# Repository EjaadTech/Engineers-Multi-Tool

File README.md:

# Engineers-Multi-Tool
yet another tool for electronics engineers to use on their workbench - planned to include Voltmeter, Ammeter, Component Tester, Serial Terminal, DAQ functionality, Waveform Generator.

A basic Arduino nano based portable device, having portable power, a basic display and circuitry to measure voltage, current, pulses, test components (Resistors, Capacitors, Transistors and more) and also be able to serve as a Serial Terminal and MORE.

## Planned Features
* Handheld formfactor - credit card/gameboy/mobile phone sized
* Arduino based
* Input Push Buttons - 6 to 10 buttons via 1 single ADC pin
* Nokia Graphics LCD - Mono, Mobile LCD for Display
* Voltage Input - 0 to 50V or possibly, -50 to 50V Voltmeter (2x)
* Current Input - 0 to 500mA or even possibly 1A Ammeter (FUSED)
* Serial Terminal - Show incoming Serial data on screen (adjustable/auto baudrate)
* Sqaure Wave Generator - basic clock generator, upto 1MHz with adjustable Duty Cycle
* Pulse Counter - Basic Pulse stats - Freq, Duty Cycle, etc
* Component Tester - a variant of the SemiConductor Tester
* Battery Powered - Chargeable via USB
* Serial Connection with PC - A basic data acquisition app on PC Side - Windows/Linux

### Suggest any other ideas that could be done..!

## TODO
* Upload Schematic
* Battery Charger integration
* Serial Terminal implementation
* Write more TODO List items...!

## WORK LOG
* Basic Circuit made on a protoboard
* LCD and Buttons Tested
* Simple Voltmeter 0.5 to 50V implemented
* Simple Pulse Generator Implemented with adjustable Freq/Duty
* Simple Menu interface implemented
* Integrate the Voltmeter, Pulse generator and Menu in one code
> DONE before 10th of June 2015

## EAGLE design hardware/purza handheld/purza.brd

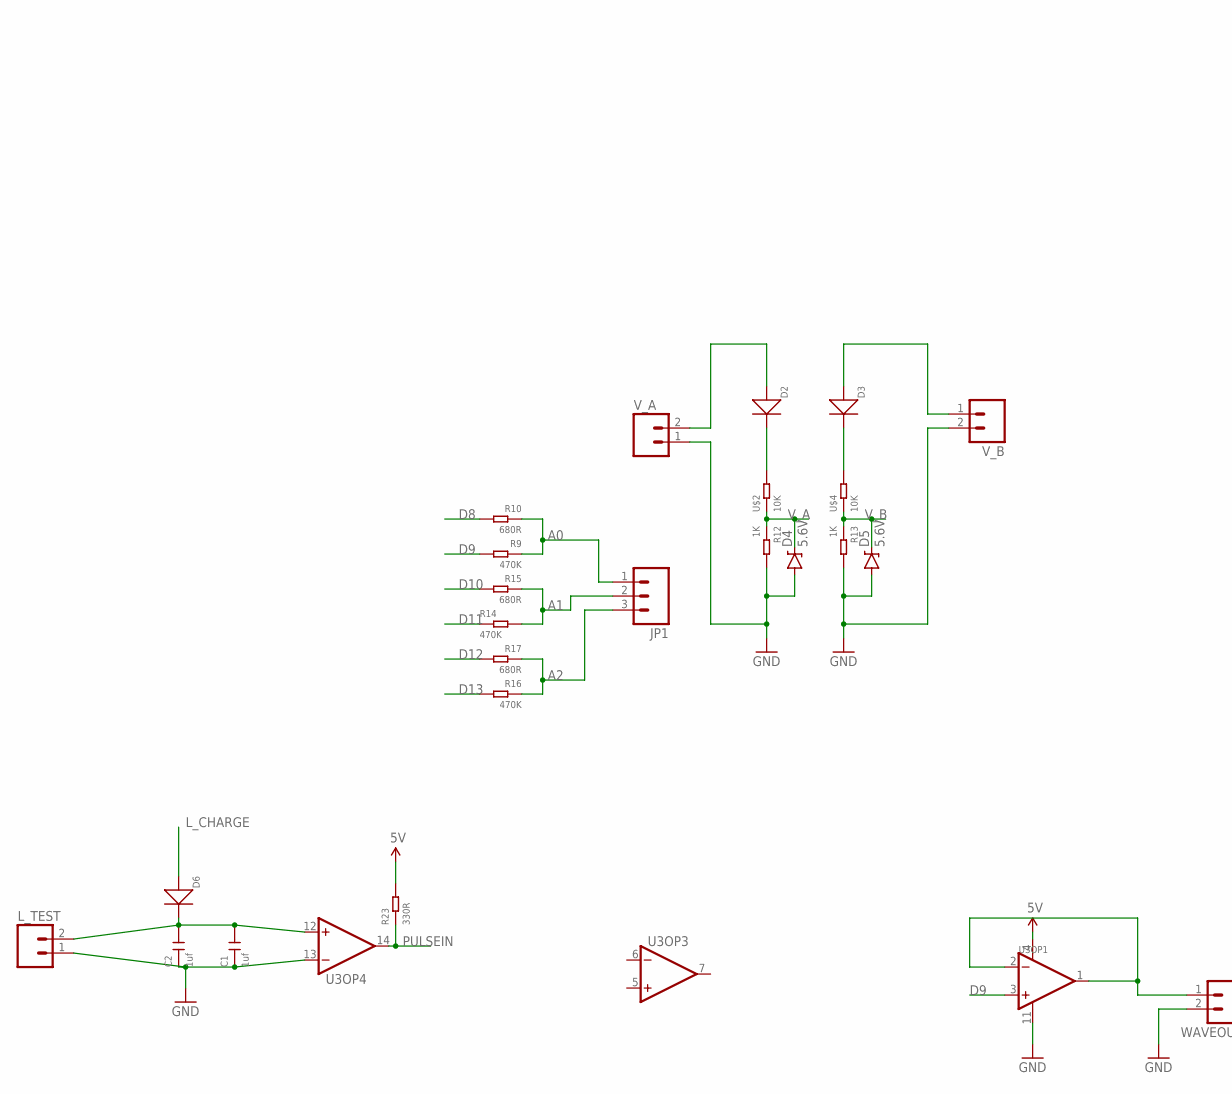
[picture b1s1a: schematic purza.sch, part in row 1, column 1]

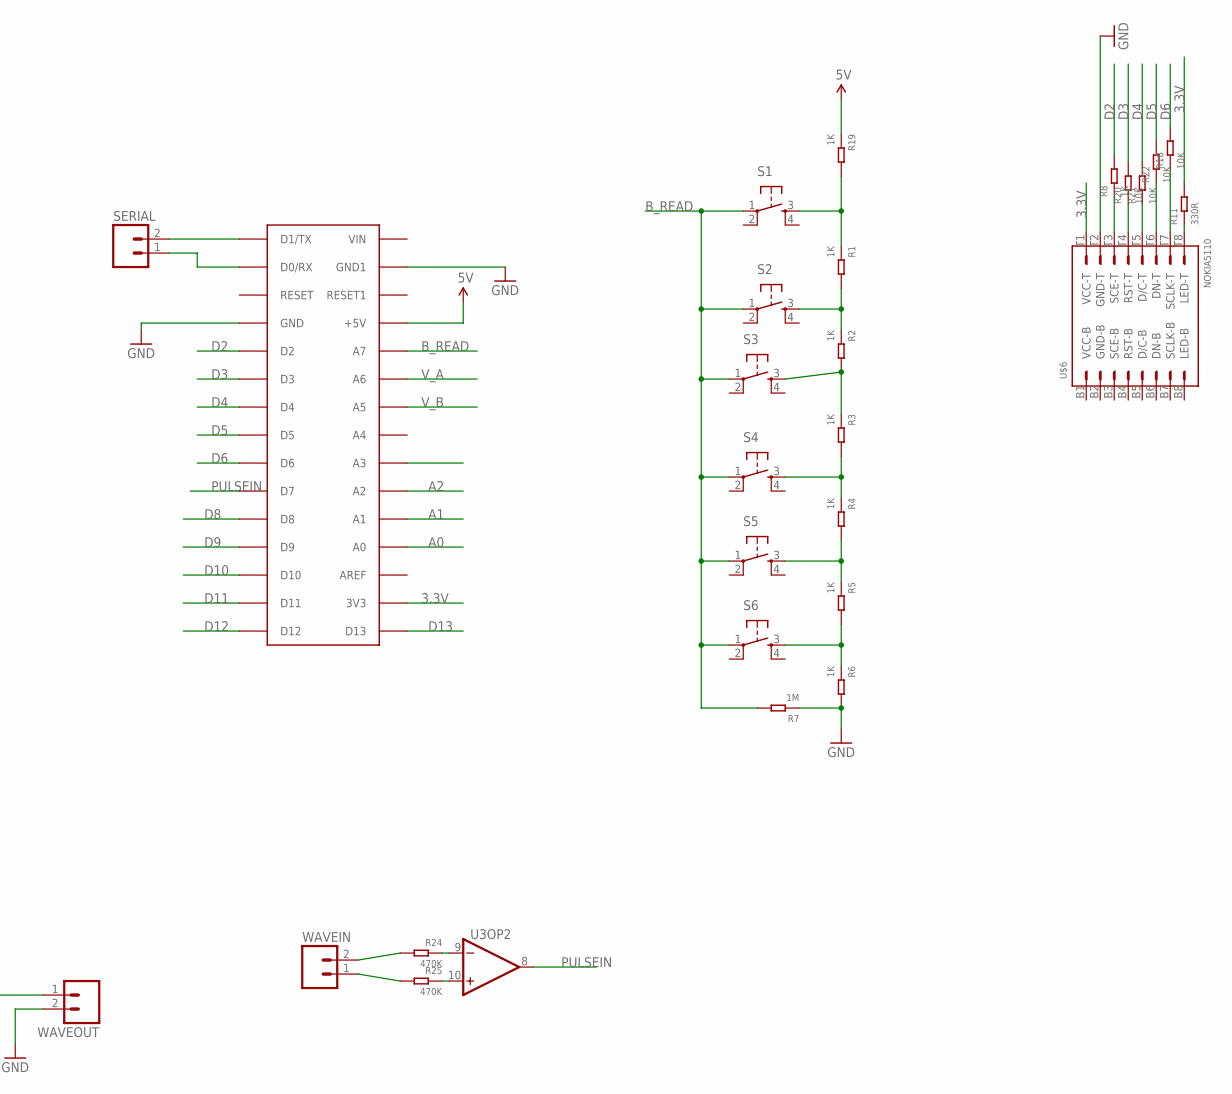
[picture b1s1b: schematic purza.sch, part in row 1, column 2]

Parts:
C1, C2: 1uf; C0805
D2, D3, D6: DIODE'1206'; SOD-123
D4, D5: 5.6V; SOD-323
JP1: M03LOCK; 1X03_LOCK
L_TEST: M02LOCK; 1X02_LOCK
R1, R2, R3, R4, R5, R6, R8, R12, R13, R19: 1K; R0603
R7: 1M; R0603
R9, R14, R16, R24, R25: 470K; R0603
R10, R15, R17: 680R; R0603
R11, R23: 330R; R0603
R18, R20, R21, R22: 10K; R0603
S1, S2, S3, S4, S5, S6: TAC_SWITCHPTH; TACTILE-PTH
SERIAL: M02LOCK; 1X02_LOCK
U3: AMPLIFIER-LMV324IDR(SOIC14); SOIC14-1.27-9.3X4.3MM
U$1: ARDUINONANO; PDIP-32
U$2, U$4: 10K; R0805
U$6: NOKIA5110
V_A: M02LOCK; 1X02_LOCK
V_B: M02LOCK; 1X02_LOCK
WAVEIN: M02LOCK; 1X02_LOCK
WAVEOUT: M02LOCK; 1X02_LOCK

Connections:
3.3V: R11.2, U$1.3V3, U$6.T1 (VCC-T)
5V: R19.1, R23.2, U3.4 (V+), U$1.+5V
A0: JP1.1, R9.1, R10.1, U$1.A0
A1: JP1.2, R14.2, R15.1, U$1.A1
A2: JP1.3, R16.1, R17.1, U$1.A2
B_READ: R7.2, S1.1, S2.1, S3.1, S4.1, S5.1, S6.1, U$1.A7
D2: R8.2, U$1.D2
D3: R20.2, U$1.D3
D4: R21.2, U$1.D4
D5: R22.2, U$1.D5
D6: R18.2, U$1.D6
D8: R10.2, U$1.D8
D9: R9.2, U3.3 (IN+), U$1.D9
D10: R15.2, U$1.D10
D11: R14.1, U$1.D11
D12: R17.2, U$1.D12
D13: R16.2, U$1.D13
GND: C1.1, C2.1, D4.A, D5.A, L_TEST.1, R6.2, R7.1, R12.2, R13.2, U3.11 (V-), U3.13 (IN-), U$1.GND, U$1.GND1, U$6.T2 (GND-T), V_A.1, V_B.2, WAVEOUT.2
L_CHARGE: D6.+, U$1.A3
unnamed: D2.-, U$2.2
unnamed: D3.-, U$4.2
unnamed: R20.1, U$6.T4 (RST-T)
unnamed: R21.1, U$6.T5 (D/C-T)
unnamed: R22.1, U$6.T6 (DN-T)
unnamed: R18.1, U$6.T7 (SCLK-T)
unnamed: R11.1, U$6.T8 (LED-T)
unnamed: R8.1, U$6.T3 (SCE-T)
unnamed: D3.+, V_B.1
unnamed: R1.2, R2.1, S2.3
unnamed: R2.2, R3.1, S3.3
unnamed: R3.2, R4.1, S4.3
unnamed: R4.2, R5.1, S5.3
unnamed: SERIAL.2, U$1.D1/TX
unnamed: SERIAL.1, U$1.D0/RX
unnamed: R1.1, R19.2, S1.3
unnamed: D2.+, V_A.2
unnamed: U3.1 (OUT), U3.2 (IN-), WAVEOUT.1
unnamed: C1.2, C2.2, D6.-, L_TEST.2, U3.12 (IN+)
unnamed: R24.2, WAVEIN.2
unnamed: R25.2, WAVEIN.1
unnamed: R25.1, U3.10 (IN+)
unnamed: R24.1, U3.9 (IN-)
unnamed: R5.2, R6.1, S6.3
PULSEIN: R23.1, U3.8 (OUT), U3.14 (OUT), U$1.D7
V_A: D4.C, R12.1, U$1.A6, U$2.1
V_B: D5.C, R13.1, U$1.A5, U$4.1

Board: 2 copper layers, 50 parts (9 on the bottom side), 46 nets, no tracks yet.

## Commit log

2015-06-09 Initial Commit - Menu Testing, Voltmeter+WaveGen. done already
    Not so initial already tested voltmeter & square wave generator - current commit only shows the menu currently in testing
2015-06-09 added hardware images - first prototype
2015-06-09 bitmap up and down update
2015-06-09 Make Display In Array
2015-06-09 Finish With LCD Animation
2015-06-09 Sync 2 Function with UI
2015-06-10 Updated README file
    Added Description, Planned Features, TODO and Work Done.
2015-06-10 More images added :)
2015-06-10 Serial Integerated with UI but Some Display Bugs
2015-06-11 Serial Display and Performance Bug Pix
2015-06-22 component tester include with main file but size issue
2015-06-22 Change bmp to simple text but still running out of memory
2015-06-22 Revert "Change bmp to simple text but still running out of memory"
    This reverts commit bb7e83f6d62d605439a3e98b5dcddaa700df4024.
2015-06-23 Run Out Of Memory Switch To Text format
2015-06-23 Done With Text Display
2015-06-30 PCB Schematic

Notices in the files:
parts and their libraries:
SparkFun-Connectors: Licensing: Creative Commons ShareAlike 4.0 International - https://creativecommons.org/licenses/by-sa/4.0
